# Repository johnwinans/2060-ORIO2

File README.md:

# ORIO2
Open Robot IO Controller Version 2 Rev 2.

A [PDF of the schematic can be found here](2060-ORIO2.pdf).

This project contains 
[KiCad 5](https://kicad.org/) 
design files for a 
[Rasbperry PI](https://www.raspberrypi.org/products/)
add-on module that can be used to operate a robot such as those used in 
[First Robotics Competition](https://www.firstinspires.org/robotics/frc).

The ORIO2 adds the following I/O ports to a Raspberry PI:

* 10 5V tolerant LVTTL quadrature inputs with 3.3v or 5v power
* 8 5V tolerant LVTTL digital inputs with 3.3v or 5v power
* 8 LVTTL digital outputs with 3.3v or 5v power
* 16 direct-FPGA GPIO pins on header with 3.3v power
* 1 Power LED
* 8 User LED outputs
* 8 User switch (binary inputs)
* 2 User push-button (binary inputs)
* 8 ADC inputs 0-5V (w/jumper on port 0 to monitor battery voltage)
* 16 PWM outputs w/6V, 3A power
* 1 12V RSL light output
* 8 24V solenoid outputs
* 1 12V air-compressor relay control output
* 1 Raspberry PI I2C pinout with 3.3V power supply & pullup resistors

All I/O is controlled with a Lattice ICE40HX4K-TQ144 FPGA that 
communicates with the PI using the PI's SPI port.

The FPGA and Raspberry PI source code is open-source and managed 
using a github repo here: 
[ORIO2-software](https://github.com/johnwinans/ORIO2-software)

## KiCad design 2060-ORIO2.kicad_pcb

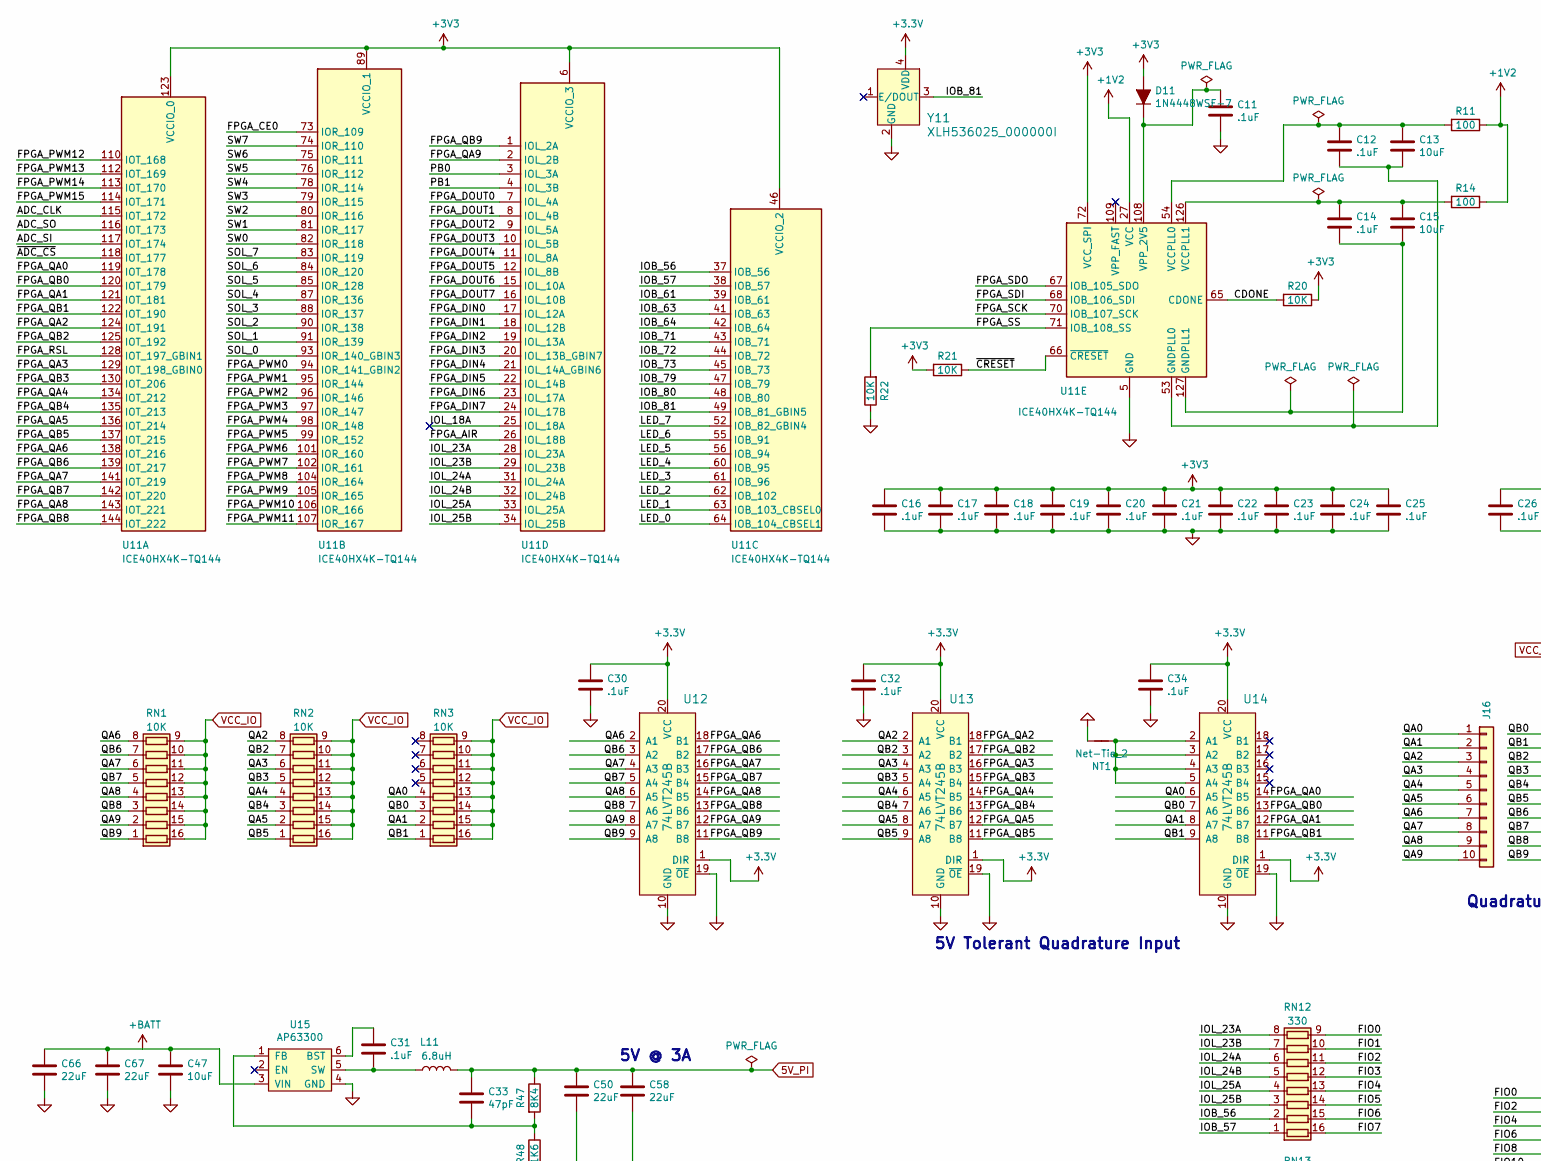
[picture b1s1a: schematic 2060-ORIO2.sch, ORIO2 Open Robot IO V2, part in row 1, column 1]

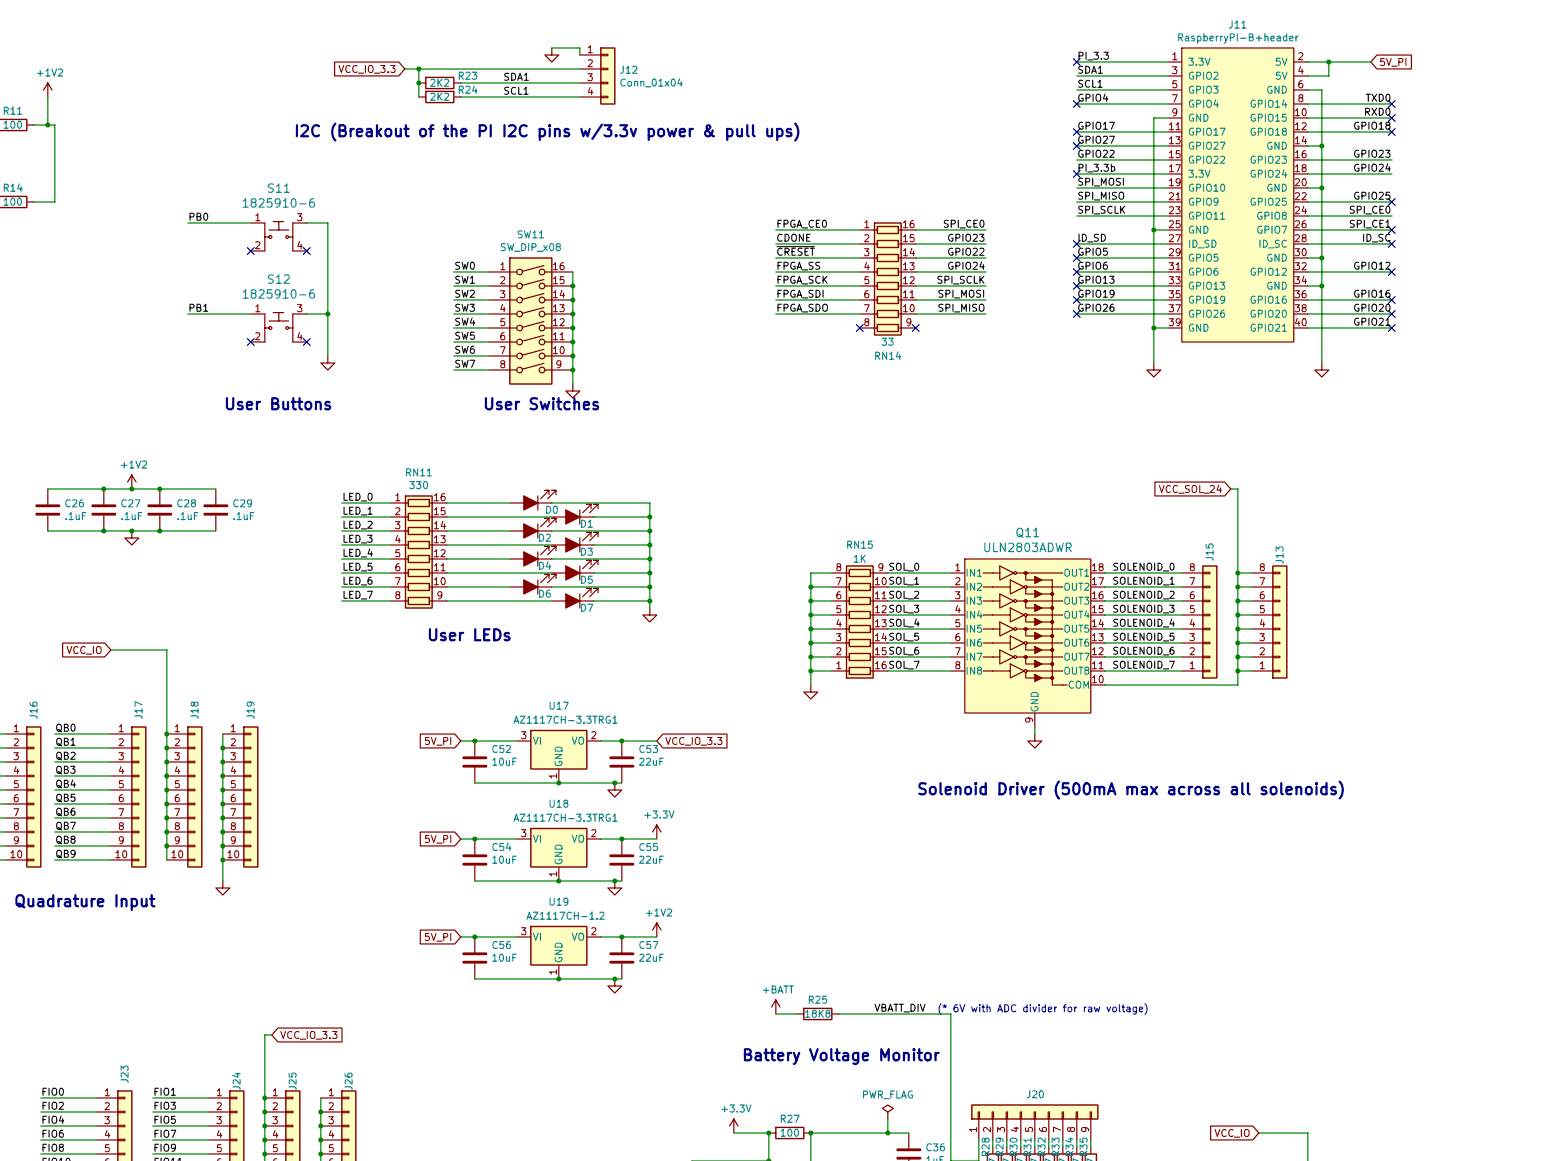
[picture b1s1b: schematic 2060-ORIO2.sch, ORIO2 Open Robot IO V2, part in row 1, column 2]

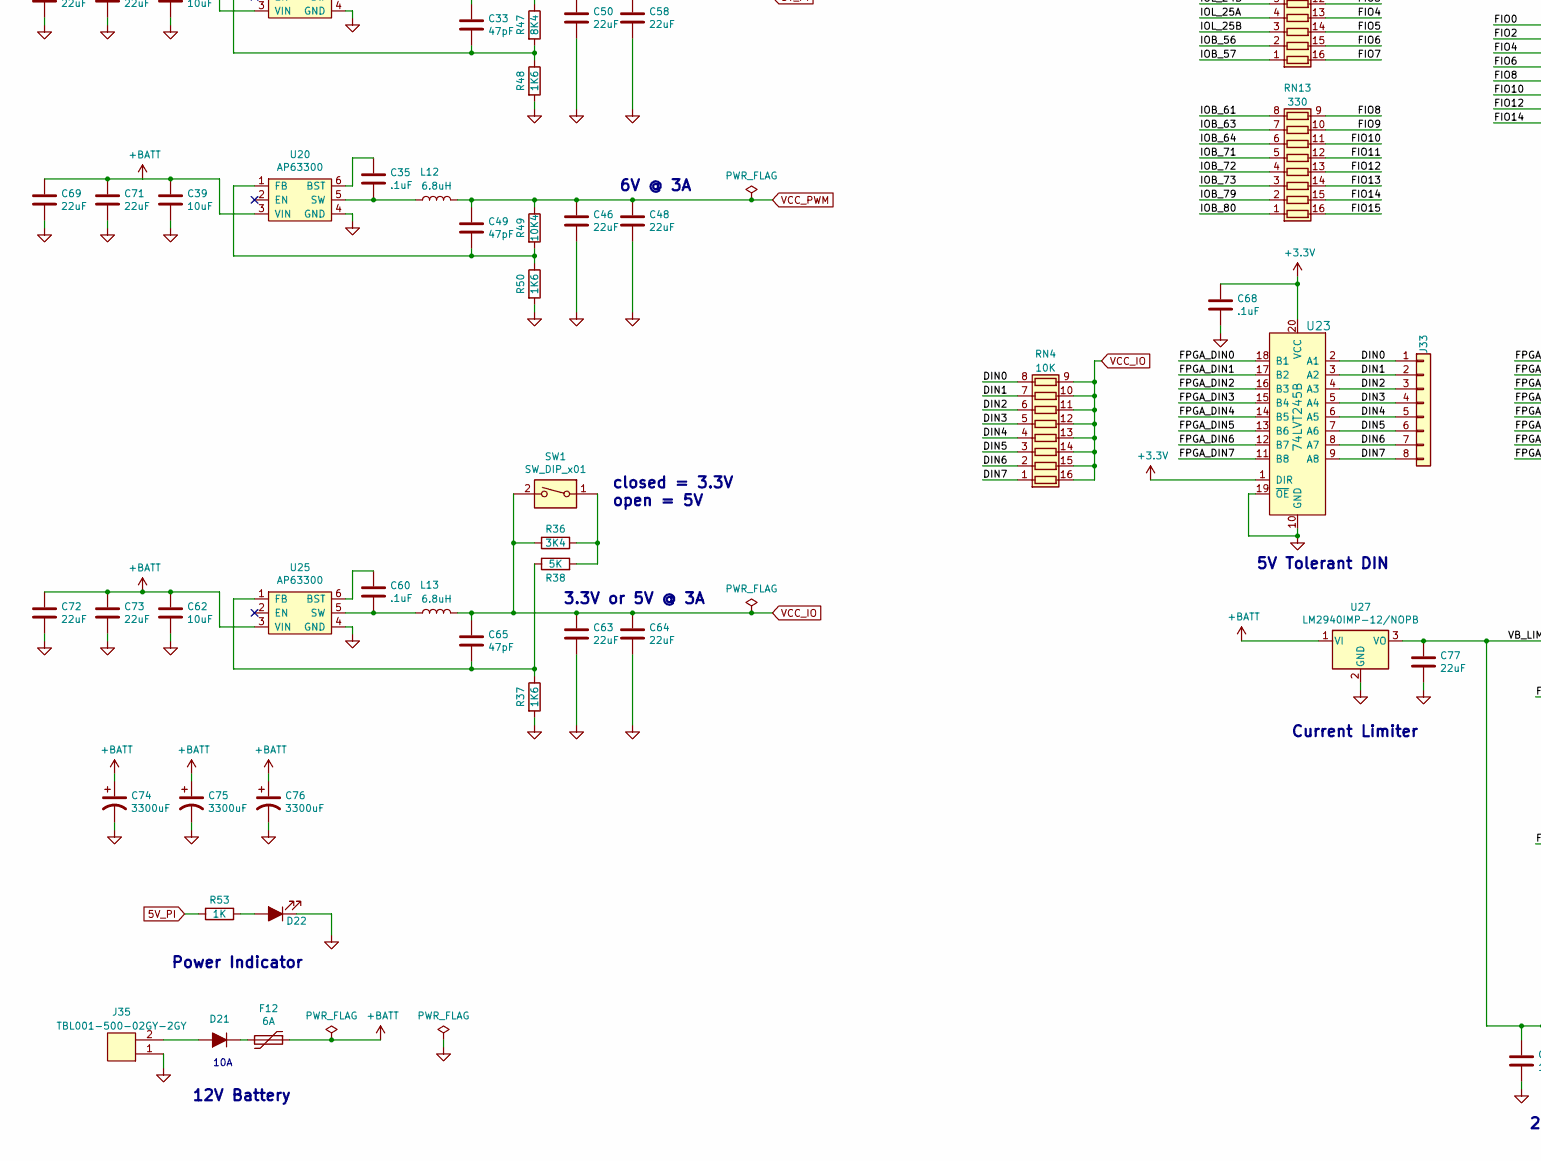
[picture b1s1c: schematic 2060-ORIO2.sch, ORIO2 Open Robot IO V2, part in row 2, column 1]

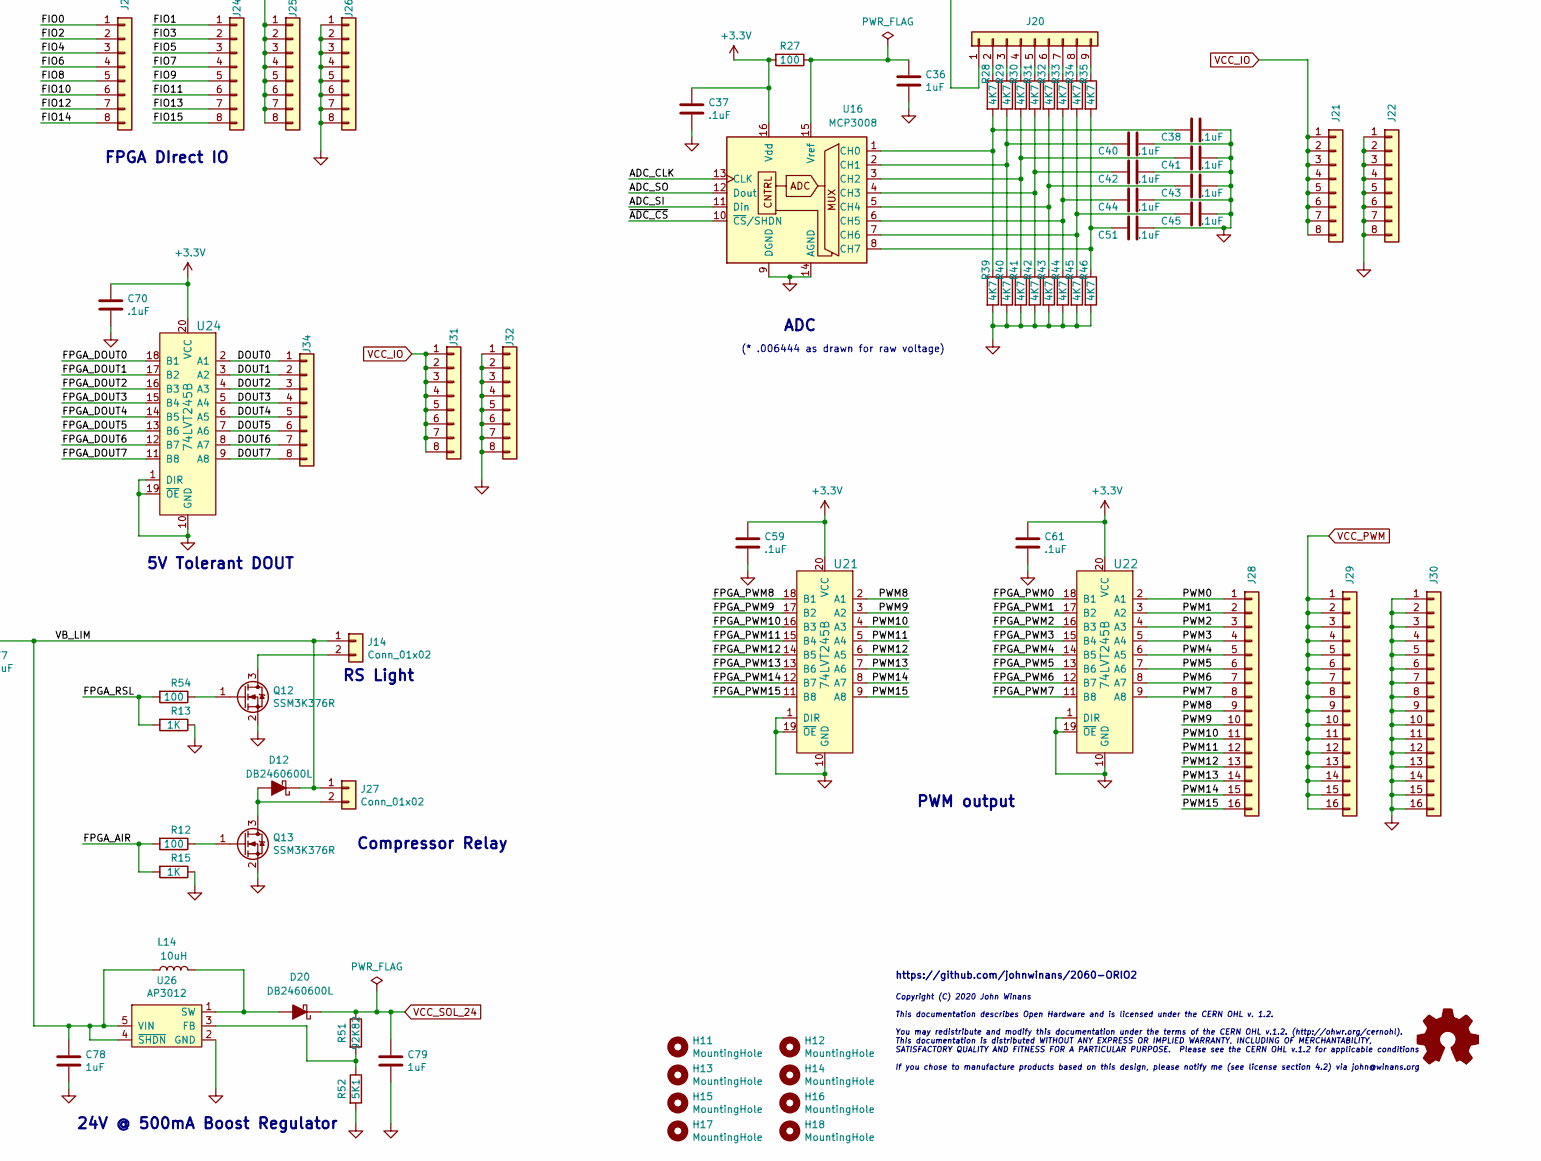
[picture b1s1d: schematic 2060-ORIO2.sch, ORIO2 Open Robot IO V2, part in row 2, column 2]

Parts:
C11, C12, C14, C16, C17, C18, C19, C20, C21, C22, C23, C24, C25, C26, C27, C28, C29, C30, C31, C32, C34, C35, C37, C38, C40, C41, C42, C43, C44, C45, C51, C59, C60, C61, C68, C70: .1uF; C_0603_1608Metric_Pad1.05x0.95mm_HandSolder; MPN C1608X5R1E104K; Digi-Key_PN 445-6854-1-ND
C13, C15, C52, C54, C56: 10uF; C_0603_1608Metric_Pad1.05x0.95mm_HandSolder; MPN CL10A106MQ8NNNC; Digi-Key_PN 1276-1119-1-ND
C33, C49, C65: 47pF; C_0603_1608Metric_Pad1.05x0.95mm_HandSolder
C36, C78, C79: 1uF; C_0603_1608Metric_Pad1.05x0.95mm_HandSolder; MPN CL10A105KA8NNNC; Digi-Key_PN 1276-1102-1-ND
C39, C47, C62: 10uF; C_0805_2012Metric_Pad1.15x1.40mm_HandSolder
C46, C48, C50, C58, C63, C64: 22uF; C_0805_2012Metric_Pad1.15x1.40mm_HandSolder; MPN GRM21BR61A226ME44L; Digi-Key_PN 490-10746-1-ND
C53, C55, C57: 22uF; C_0603_1608Metric_Pad1.05x0.95mm_HandSolder; MPN CL10A226MQ8NRNE; Digi-Key_PN 1276-2868-1-ND
C66, C67, C69, C71, C72, C73, C77: 22uF; C_0805_2012Metric_Pad1.15x1.40mm_HandSolder; Digi-Key_PN 490-14661-1-ND
C74, C75, C76: 3300uF; CP_Radial_D16.0mm_P7.50mm; MPN UVR1E332MHD; Digi-Key_PN 493-1067-ND
D0, D1, D2, D3, D4, D5, D6, D7, D22: LED_ALT; LED_0805_2012Metric_Pad1.15x1.40mm_HandSolder; MPN LG R971-KN-1; Digi-Key_PN 475-1410-1-ND
D11: 1N4448WSF-7; D_0603_1608Metric_Pad1.05x0.95mm_HandSolder; MPN 1N4448HWS-7-F; Digi-Key_PN 1N4448HWS-FDICT-ND
D12, D20: DB2460600L; D_SOD-128; MPN DB2460600L; Digi-Key_PN DB2460600LCT-ND
D21: D_ALT; D_SMC; MPN S10KC V7G; Digi-Key_PN S10KCV7GCT-ND
F12: 6A; Fuse_2920_7451Metric_Pad2.10x5.45mm_HandSolder; MPN 2920L600/12MR; Digi-Key_PN F8137CT-ND
H11, H12, H13, H14, H15, H16, H17, H18: MountingHole; MountingHole_2.7mm_M2.5; MPN x; Digi-Key_PN x
J11: RaspberryPI-B+header; PinHeader_2x20_P2.54mm_Vertical; MPN x; Digi-Key_PN x
J12: Conn_01x04; PinHeader_1x04_P2.54mm_Vertical; MPN x; Digi-Key_PN x
J13, J15, J21, J22, J23, J24, J25, J26, J31, J32, J33, J34: Conn_01x08; PinHeader_1x08_P2.54mm_Vertical; MPN x; Digi-Key_PN x
J14, J27: Conn_01x02; PinHeader_1x02_P2.54mm_Vertical; MPN x; Digi-Key_PN x
J16, J17, J18, J19: Conn_01x10; PinHeader_1x10_P2.54mm_Vertical; MPN x; Digi-Key_PN x
J20: Conn_01x09; PinHeader_1x09_P2.54mm_Vertical; MPN x; Digi-Key_PN x
J28, J29, J30: Conn_01x16; PinHeader_1x16_P2.54mm_Vertical; MPN x; Digi-Key_PN x
J35: TBL001-500-02GY-2GY; MPN TBL001-500-02GY-2GY; Digi-Key_PN 102-6360-ND
L11, L12, L13: 6.8uH; L_Bourns-SRN6028; MPN VLS6045EX-6R8M; Digi-Key_PN 445-173057-1-ND
L14: 10uH; L_Taiyo-Yuden_NR-40xx_HandSoldering; MPN NRG4026T100M; Digi-Key_PN 587-2376-1-ND
LOGO11: Logo_Open_Hardware_Small; OSHW-Logo_11.4x12mm_SilkScreen; MPN x; Digi-Key_PN x
NT1: Net-Tie_2; NetTie-2_SMD_Pad0.5mm; MPN x; Digi-Key_PN x
Q11: ULN2803ADWR; SOIC-18_W7.5mm; MPN ULN2803ADWR; Digi-Key_PN 296-15777-1-ND
Q12, Q13: SSM3K376R; SOT-23; MPN ‎SSM3K376R,LF; Digi-Key_PN SSM3K376RLFCT-ND‎
R11, R14, R27: 100; R_0603_1608Metric_Pad1.05x0.95mm_HandSolder; MPN RC0603FR-07100RL; Digi-Key_PN 311-100HRCT-ND
R12, R54: 100; R_0603_1608Metric_Pad0.98x0.95mm_HandSolder; MPN RC0603FR-07100RL; Digi-Key_PN 311-100HRCT-ND
R13, R15: 1K; R_0603_1608Metric_Pad0.98x0.95mm_HandSolder
R20, R21, R22: 10K; R_0603_1608Metric_Pad1.05x0.95mm_HandSolder; MPN RC0603FR-0710KL; Digi-Key_PN 311-10.0KHRCT-ND
R23, R24: 2K2; R_0603_1608Metric_Pad1.05x0.95mm_HandSolder; MPN RC0603FR-072K2L; Digi-Key_PN 311-2.20KHRCT-ND
R25: 18K8; R_0603_1608Metric_Pad1.05x0.95mm_HandSolder; MPN RC0603FR-0718KL; Digi-Key_PN 311-18.0KHRCT-ND
R28, R29, R30, R31, R32, R33, R34, R35, R39, R40, R41, R42, R43, R44, R45, R46: 4K7; R_0603_1608Metric_Pad1.05x0.95mm_HandSolder; MPN RC0603FR-074K7L; Digi-Key_PN 311-4.70KHRCT-ND
R36: 3K4; R_0603_1608Metric_Pad1.05x0.95mm_HandSolder; MPN RMCF0603FT3K40; Digi-Key_PN RMCF0603FT3K40CT-ND
R37, R48, R50: 1K6; R_0603_1608Metric_Pad1.05x0.95mm_HandSolder; MPN RMCF0603FT1K60; Digi-Key_PN RMCF0603FT1K60CT-ND
R38: 5K; R_0603_1608Metric_Pad1.05x0.95mm_HandSolder; MPN CR0603-FX-5101ELF; Digi-Key_PN CR0603-FX-5101ELFCT-ND
R47: 8K4; R_0603_1608Metric_Pad1.05x0.95mm_HandSolder; MPN RMCF0603FT8K45; Digi-Key_PN RMCF0603FT8K45CT-ND
R49: 10K4; R_0603_1608Metric_Pad1.05x0.95mm_HandSolder; MPN RMCF0603FT10K5; Digi-Key_PN RMCF0603FT10K5CT-ND
R51: 92K82; R_0603_1608Metric_Pad1.05x0.95mm_HandSolder; MPN RMCF0603FT90K9; Digi-Key_PN RMCF0603FT90K9CT-ND
R52: 5K1; R_0603_1608Metric_Pad1.05x0.95mm_HandSolder; MPN CR0603-FX-5101ELF; Digi-Key_PN CR0603-FX-5101ELFCT-ND
R53: 1K; R_0603_1608Metric_Pad1.05x0.95mm_HandSolder; MPN RC0603FR-071KL; Digi-Key_PN 311-1.00KHRCT-ND
RN1, RN2, RN3, RN4: 10K; R_Array_Convex_8x0602; MPN EXB-2HV103JV; Digi-Key_PN Y1103CT-ND
RN11, RN12, RN13: 330; R_Array_Convex_8x0602; MPN EXB-2HV331JV; Digi-Key_PN Y1331CT-ND
RN14: 33; R_Array_Convex_8x0602; MPN EXB-2HV330JV; Digi-Key_PN Y1330CT-ND
RN15: 1K; R_Array_Convex_8x0602; MPN EXB-2HV102JV; Digi-Key_PN Y1102CT-ND
S11, S12: 1825910-6; Switch_Tactile_THT_6x6mm; MPN 1825910-6; Digi-Key_PN 450-1650-ND
SW1: SW_DIP_x01; SW_DIP_SPSTx01_Slide_6.7x4.1mm_W7.62mm_P2.54mm_LowProfile; MPN DS04-254-1L-01BK; Digi-Key_PN 2223-DS04-254-1L-01BK-ND
SW11: SW_DIP_x08; SW_DIP_SPSTx08_Slide_6.7x21.88mm_W7.62mm_P2.54mm_LowProfile; MPN 210-8MS; Digi-Key_PN CT2108MS-ND
U11: ICE40HX4K-TQ144; TQFP-144_20x20mm_P0.5mm; MPN ICE40HX4K-TQ144; Digi-Key_PN 220-1572-ND
U12, U13, U14, U21, U22, U23, U24: ‎74LVT245B; TSSOP-20_4.4x6.5mm_P0.65mm; MPN 74LVT245BPW,118; Digi-Key_PN 1727-6005-1-ND
U15, U20, U25: AP63300; SOT-23-6; MPN AP63300WU-7; Digi-Key_PN 31-AP63300WU-7CT-ND
U16: MCP3008; SOIC-16_3.9x9.9mm_P1.27mm; MPN MCP3008-I/SL; Digi-Key_PN MCP3008-I/SL-ND
U17, U18: AZ1117CH-3.3TRG1; SOT-223-3_TabPin2; MPN AZ1117CH-3.3TRG1; Digi-Key_PN AZ1117CH-3.3TRG1DICT-ND
U19: AZ1117CH-1.2; SOT-223-3_TabPin2; MPN AZ1117CH-1.2TRG1; Digi-Key_PN AZ1117CH-1.2TRG1DICT-ND
U26: AP3012; SOT-23-5; MPN AP3012KTR-G1; Digi-Key_PN AP3012KTR-G1DICT-ND
U27: LM2940IMP-12/NOPB; TO-252-3_TabPin2; MPN LM2940IMP-12/NOPB; Digi-Key_PN LM2940IMP-12/NOPBCT-ND
Y11: XLH536025_000000I; Oscillator_XLH536025.000000I; MPN XLH536025.000000I; Digi-Key_PN 631-1156-1-ND

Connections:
5V_PI: C33.1, C50.1, C52.1, C54.1, C56.1, C58.1, J11.2 (5V), J11.4 (5V), L11.2, R47.1, R53.2, U17.3 (VI), U18.3 (VI), U19.3 (VI)
+1V2: C26.1, C27.1, C28.1, C29.1, C57.1, R11.1, R14.1, U11.27 (VCC), U11.40 (VCC), U11.92 (VCC), U11.111 (VCC), U19.2 (VO)
+BATT: C39.1, C47.1, C62.1, C66.1, C67.1, C69.1, C71.1, C72.1, C73.1, C74.1, C75.1, C76.1, F12.1, R25.2, U15.3 (VIN), U20.3 (VIN), U25.3 (VIN), U27.1 (VI)
/ADC_CLK: U11.115 (IOT_172), U16.13 (CLK)
/ADC_SI: U11.117 (IOT_174), U16.11 (Din)
/ADC_SO: U11.116 (IOT_173), U16.12 (Dout)
/CDONE: R20.2, RN14.2 (R2.1), U11.65 (CDONE)
/DIN0: J33.1, RN4.8 (R8.1), U23.2 (A1)
/DIN1: J33.2, RN4.7 (R7.1), U23.3 (A2)
/DIN2: J33.3, RN4.6 (R6.1), U23.4 (A3)
/DIN3: J33.4, RN4.5 (R5.1), U23.5 (A4)
/DIN4: J33.5, RN4.4 (R4.1), U23.6 (A5)
/DIN5: J33.6, RN4.3 (R3.1), U23.7 (A6)
/DIN6: J33.7, RN4.2 (R2.1), U23.8 (A7)
/DIN7: J33.8, RN4.1 (R1.1), U23.9 (A8)
/DOUT0: J34.1, U24.2 (A1)
/DOUT1: J34.2, U24.3 (A2)
/DOUT2: J34.3, U24.4 (A3)
/DOUT3: J34.4, U24.5 (A4)
/DOUT4: J34.5, U24.6 (A5)
/DOUT5: J34.6, U24.7 (A6)
/DOUT6: J34.7, U24.8 (A7)
/DOUT7: J34.8, U24.9 (A8)
/FIO0: J23.1, RN12.9 (R8.2)
/FIO1: J24.1, RN12.10 (R7.2)
/FIO2: J23.2, RN12.11 (R6.2)
/FIO3: J24.2, RN12.12 (R5.2)
/FIO4: J23.3, RN12.13 (R4.2)
/FIO5: J24.3, RN12.14 (R3.2)
/FIO6: J23.4, RN12.15 (R2.2)
/FIO7: J24.4, RN12.16 (R1.2)
/FIO8: J23.5, RN13.9 (R8.2)
/FIO9: J24.5, RN13.10 (R7.2)
/FIO10: J23.6, RN13.11 (R6.2)
/FIO11: J24.6, RN13.12 (R5.2)
/FIO12: J23.7, RN13.13 (R4.2)
/FIO13: J24.7, RN13.14 (R3.2)
/FIO14: J23.8, RN13.15 (R2.2)
/FIO15: J24.8, RN13.16 (R1.2)
/FPGA_AIR: R12.2, R15.2, U11.26 (IOL_18B)
/FPGA_CE0: RN14.1 (R1.1), U11.73 (IOR_109)
/FPGA_DIN0: U11.17 (IOL_12A), U23.18 (B1)
/FPGA_DIN1: U11.18 (IOL_12B), U23.17 (B2)
/FPGA_DIN2: U11.19 (IOL_13A), U23.16 (B3)
/FPGA_DIN3: U11.20 (IOL_13B_GBIN7), U23.15 (B4)
/FPGA_DIN4: U11.21 (IOL_14A_GBIN6), U23.14 (B5)
/FPGA_DIN5: U11.22 (IOL_14B), U23.13 (B6)
/FPGA_DIN6: U11.23 (IOL_17A), U23.12 (B7)
/FPGA_DIN7: U11.24 (IOL_17B), U23.11 (B8)
/FPGA_DOUT0: U11.7 (IOL_4A), U24.18 (B1)
/FPGA_DOUT1: U11.8 (IOL_4B), U24.17 (B2)
/FPGA_DOUT2: U11.9 (IOL_5A), U24.16 (B3)
/FPGA_DOUT3: U11.10 (IOL_5B), U24.15 (B4)
/FPGA_DOUT4: U11.11 (IOL_8A), U24.14 (B5)
/FPGA_DOUT5: U11.12 (IOL_8B), U24.13 (B6)
/FPGA_DOUT6: U11.15 (IOL_10A), U24.12 (B7)
/FPGA_DOUT7: U11.16 (IOL_10B), U24.11 (B8)
/FPGA_PWM0: U11.94 (IOR_141_GBIN2), U22.18 (B1)
/FPGA_PWM1: U11.95 (IOR_144), U22.17 (B2)
/FPGA_PWM2: U11.96 (IOR_146), U22.16 (B3)
/FPGA_PWM3: U11.97 (IOR_147), U22.15 (B4)
/FPGA_PWM4: U11.98 (IOR_148), U22.14 (B5)
/FPGA_PWM5: U11.99 (IOR_152), U22.13 (B6)
/FPGA_PWM6: U11.101 (IOR_160), U22.12 (B7)
/FPGA_PWM7: U11.102 (IOR_161), U22.11 (B8)
/FPGA_PWM8: U11.104 (IOR_164), U21.18 (B1)
/FPGA_PWM9: U11.105 (IOR_165), U21.17 (B2)
/FPGA_PWM10: U11.106 (IOR_166), U21.16 (B3)
/FPGA_PWM11: U11.107 (IOR_167), U21.15 (B4)
/FPGA_PWM12: U11.110 (IOT_168), U21.14 (B5)
/FPGA_PWM13: U11.112 (IOT_169), U21.13 (B6)
/FPGA_PWM14: U11.113 (IOT_170), U21.12 (B7)
/FPGA_PWM15: U11.114 (IOT_171), U21.11 (B8)
/FPGA_QA0: U11.119 (IOT_178), U14.14 (B5)
/FPGA_QA1: U11.121 (IOT_181), U14.12 (B7)
/FPGA_QA2: U11.124 (IOT_191), U13.18 (B1)
/FPGA_QA3: U11.129 (IOT_198_GBIN0), U13.16 (B3)
/FPGA_QA4: U11.134 (IOT_212), U13.14 (B5)
/FPGA_QA5: U11.136 (IOT_214), U13.12 (B7)
/FPGA_QA6: U11.138 (IOT_216), U12.18 (B1)
/FPGA_QA7: U11.141 (IOT_219), U12.16 (B3)
/FPGA_QA8: U11.143 (IOT_221), U12.14 (B5)
/FPGA_QA9: U11.2 (IOL_2B), U12.12 (B7)
/FPGA_QB0: U11.120 (IOT_179), U14.13 (B6)
/FPGA_QB1: U11.122 (IOT_190), U14.11 (B8)
/FPGA_QB2: U11.125 (IOT_192), U13.17 (B2)
/FPGA_QB3: U11.130 (IOT_206), U13.15 (B4)
/FPGA_QB4: U11.135 (IOT_213), U13.13 (B6)
/FPGA_QB5: U11.137 (IOT_215), U13.11 (B8)
/FPGA_QB6: U11.139 (IOT_217), U12.17 (B2)
/FPGA_QB7: U11.142 (IOT_220), U12.15 (B4)
/FPGA_QB8: U11.144 (IOT_222), U12.13 (B6)
/FPGA_QB9: U11.1 (IOL_2A), U12.11 (B8)
/FPGA_RSL: R13.2, R54.2, U11.128 (IOT_197_GBIN1)
/FPGA_SCK: RN14.5 (R5.1), U11.70 (IOB_107_SCK)
/FPGA_SDI: RN14.6 (R6.1), U11.68 (IOB_106_SDI)
/FPGA_SDO: RN14.7 (R7.1), U11.67 (IOB_105_SDO)
/FPGA_SS: R22.2, RN14.4 (R4.1), U11.71 (IOB_108_SS)
/GPIO4: J11.7 (GPIO4)
/GPIO5: J11.29 (GPIO5)
/GPIO6: J11.31 (GPIO6)
/GPIO12: J11.32 (GPIO12)
/GPIO13: J11.33 (GPIO13)
/GPIO16: J11.36 (GPIO16)
/GPIO17: J11.11 (GPIO17)
/GPIO18: J11.12 (GPIO18)
/GPIO19: J11.35 (GPIO19)
/GPIO20: J11.38 (GPIO20)
/GPIO21: J11.40 (GPIO21)
/GPIO22: J11.15 (GPIO22), RN14.14 (R3.2)
/GPIO23: J11.16 (GPIO23), RN14.15 (R2.2)
/GPIO24: J11.18 (GPIO24), RN14.13 (R4.2)
/GPIO25: J11.22 (GPIO25)
/GPIO26: J11.37 (GPIO26)
/GPIO27: J11.13 (GPIO27)
/ID_SC: J11.28 (ID_SC)
/ID_SD: J11.27 (ID_SD)
/IOB_56: RN12.2 (R2.1), U11.37 (IOB_56)
/IOB_57: RN12.1 (R1.1), U11.38 (IOB_57)
/IOB_61: RN13.8 (R8.1), U11.39 (IOB_61)
/IOB_63: RN13.7 (R7.1), U11.41 (IOB_63)
/IOB_64: RN13.6 (R6.1), U11.42 (IOB_64)
/IOB_71: RN13.5 (R5.1), U11.43 (IOB_71)
/IOB_72: RN13.4 (R4.1), U11.44 (IOB_72)
/IOB_73: RN13.3 (R3.1), U11.45 (IOB_73)
/IOB_79: RN13.2 (R2.1), U11.47 (IOB_79)
/IOB_80: RN13.1 (R1.1), U11.48 (IOB_80)
/IOB_81: U11.49 (IOB_81_GBIN5), Y11.3 (OUT)
/IOL_18A: U11.25 (IOL_18A)
/IOL_23A: RN12.8 (R8.1), U11.28 (IOL_23A)
/IOL_23B: RN12.7 (R7.1), U11.29 (IOL_23B)
/IOL_24A: RN12.6 (R6.1), U11.31 (IOL_24A)
/IOL_24B: RN12.5 (R5.1), U11.32 (IOL_24B)
/IOL_25A: RN12.4 (R4.1), U11.33 (IOL_25A)
/IOL_25B: RN12.3 (R3.1), U11.34 (IOL_25B)
/LED_0: RN11.1 (R1.1), U11.64 (IOB_104_CBSEL1)
/LED_1: RN11.2 (R2.1), U11.63 (IOB_103_CBSEL0)
/LED_2: RN11.3 (R3.1), U11.62 (IOB_102)
/LED_3: RN11.4 (R4.1), U11.61 (IOB_96)
/LED_4: RN11.5 (R5.1), U11.60 (IOB_95)
/LED_5: RN11.6 (R6.1), U11.56 (IOB_94)
/LED_6: RN11.7 (R7.1), U11.55 (IOB_91)
/LED_7: RN11.8 (R8.1), U11.52 (IOB_82_GBIN4)
/PB0: S11.1, U11.3 (IOL_3A)
/PB1: S12.1, U11.4 (IOL_3B)
/PI_3.3: J11.1 (3.3V)
/PI_3.3b: J11.17 (3.3V)
/PWM0: J28.1, U22.2 (A1)
/PWM1: J28.2, U22.3 (A2)
/PWM2: J28.3, U22.4 (A3)
/PWM3: J28.4, U22.5 (A4)
/PWM4: J28.5, U22.6 (A5)
/PWM5: J28.6, U22.7 (A6)
/PWM6: J28.7, U22.8 (A7)
/PWM7: J28.8, U22.9 (A8)
/PWM8: J28.9, U21.2 (A1)
/PWM9: J28.10, U21.3 (A2)
/PWM10: J28.11, U21.4 (A3)
/PWM11: J28.12, U21.5 (A4)
/PWM12: J28.13, U21.6 (A5)
/PWM13: J28.14, U21.7 (A6)
/PWM14: J28.15, U21.8 (A7)
/PWM15: J28.16, U21.9 (A8)
/QA0: J16.1, RN3.4 (R4.1), U14.6 (A5)
/QA1: J16.2, RN3.2 (R2.1), U14.8 (A7)
/QA2: J16.3, RN2.8 (R8.1), U13.2 (A1)
/QA3: J16.4, RN2.6 (R6.1), U13.4 (A3)
/QA4: J16.5, RN2.4 (R4.1), U13.6 (A5)
/QA5: J16.6, RN2.2 (R2.1), U13.8 (A7)
/QA6: J16.7, RN1.8 (R8.1), U12.2 (A1)
/QA7: J16.8, RN1.6 (R6.1), U12.4 (A3)
/QA8: J16.9, RN1.4 (R4.1), U12.6 (A5)
/QA9: J16.10, RN1.2 (R2.1), U12.8 (A7)
/QB0: J17.1, RN3.3 (R3.1), U14.7 (A6)
/QB1: J17.2, RN3.1 (R1.1), U14.9 (A8)
/QB2: J17.3, RN2.7 (R7.1), U13.3 (A2)
/QB3: J17.4, RN2.5 (R5.1), U13.5 (A4)
/QB4: J17.5, RN2.3 (R3.1), U13.7 (A6)
/QB5: J17.6, RN2.1 (R1.1), U13.9 (A8)
/QB6: J17.7, RN1.7 (R7.1), U12.3 (A2)
/QB7: J17.8, RN1.5 (R5.1), U12.5 (A4)
/QB8: J17.9, RN1.3 (R3.1), U12.7 (A6)
/QB9: J17.10, RN1.1 (R1.1), U12.9 (A8)
/RXD0: J11.10 (GPIO15)
/SCL1: J11.5 (GPIO3), J12.4, R24.1
/SDA1: J11.3 (GPIO2), J12.3, R23.1
/SOLENOID_0: J15.8, Q11.18 (OUT1)
/SOLENOID_1: J15.7, Q11.17 (OUT2)
/SOLENOID_2: J15.6, Q11.16 (OUT3)
/SOLENOID_3: J15.5, Q11.15 (OUT4)
/SOLENOID_4: J15.4, Q11.14 (OUT5)
/SOLENOID_5: J15.3, Q11.13 (OUT6)
/SOLENOID_6: J15.2, Q11.12 (OUT7)
/SOLENOID_7: J15.1, Q11.11 (OUT8)
/SOL_0: Q11.1 (IN1), RN15.9 (R8.2), U11.93 (IOR_140_GBIN3)
/SOL_1: Q11.2 (IN2), RN15.10 (R7.2), U11.91 (IOR_139)
/SOL_2: Q11.3 (IN3), RN15.11 (R6.2), U11.90 (IOR_138)
/SOL_3: Q11.4 (IN4), RN15.12 (R5.2), U11.88 (IOR_137)
/SOL_4: Q11.5 (IN5), RN15.13 (R4.2), U11.87 (IOR_136)
/SOL_5: Q11.6 (IN6), RN15.14 (R3.2), U11.85 (IOR_128)
/SOL_6: Q11.7 (IN7), RN15.15 (R2.2), U11.84 (IOR_120)
/SOL_7: Q11.8 (IN8), RN15.16 (R1.2), U11.83 (IOR_119)
/SPI_CE0: J11.24 (GPIO8), RN14.16 (R1.2)
/SPI_CE1: J11.26 (GPIO7)
/SPI_MISO: J11.21 (GPIO9), RN14.10 (R7.2)
/SPI_MOSI: J11.19 (GPIO10), RN14.11 (R6.2)
/SPI_SCLK: J11.23 (GPIO11), RN14.12 (R5.2)
/SW0: SW11.1, U11.82 (IOR_118)
/SW1: SW11.2, U11.81 (IOR_117)
/SW2: SW11.3, U11.80 (IOR_116)
/SW3: SW11.4, U11.79 (IOR_115)
/SW4: SW11.5, U11.78 (IOR_114)
/SW5: SW11.6, U11.76 (IOR_112)
/SW6: SW11.7, U11.75 (IOR_111)
/SW7: SW11.8, U11.74 (IOR_110)
/TXD0: J11.8 (GPIO14)
/VBATT_DIV: J20.1, R25.1
/VB_LIM: C77.1, C78.1, D12.1 (K), J14.1, J27.1, L14.1, U26.4 (~SHDN), U26.5 (VIN), U27.3 (VO)
/~ADC_CS: U11.118 (IOT_177), U16.10 (~CS~/SHDN)
/~CRESET~: R21.1, RN14.3 (R3.1), U11.66 (~CRESET)
GND: C11.2, C16.2, C17.2, C18.2, C19.2, C20.2, C21.2, C22.2, C23.2, C24.2, C25.2, C26.2, C27.2, C28.2, C29.2, C30.2, C32.2, C34.2, C36.2, C37.2, C38.2, C39.2, C40.2, C41.2, C42.2, C43.2, C44.2, C45.2, C46.2, C47.2, C48.2, C50.2, C51.2, C52.2, C53.2, C54.2, C55.2, C56.2, C57.2, C58.2, C59.2, C61.2, C62.2, C63.2, C64.2, C66.2, C67.2, C68.2, C69.2, C70.2, C71.2, C72.2, C73.2, C74.2, C75.2, C76.2, C77.2, C78.2, C79.2, D0.1 (K), D1.1 (K), D2.1 (K), D3.1 (K), D4.1 (K), D5.1 (K), D6.1 (K), D7.1 (K), D22.1 (K), J11.6 (GND), J11.9 (GND), J11.14 (GND), J11.20 (GND), J11.25 (GND), J11.30 (GND), J11.34 (GND), J11.39 (GND), J12.1, J19.1, J19.2, J19.3, J19.4, J19.5, J19.6, J19.7, J19.8, J19.9, J19.10, J22.1, J22.2, J22.3, J22.4, J22.5, J22.6, J22.7, J22.8, J26.1, J26.2, J26.3, J26.4, J26.5, J26.6, J26.7, J26.8, J30.1, J30.2, J30.3, J30.4, J30.5, J30.6, J30.7, J30.8, J30.9, J30.10, J30.11, J30.12, J30.13, J30.14, J30.15, J30.16, J32.1, J32.2, J32.3, J32.4, J32.5, J32.6, J32.7, J32.8, J35.1, NT1.1, Q11.9 (GND), Q12.2 (S), Q13.2 (S), R13.1, R15.1, R22.1, R37.2, R39.2, R40.2, R41.2, R42.2, R43.2, R44.2, R45.2, R46.2, R48.2, R50.2, R52.2, RN15.1 (R1.1), RN15.2 (R2.1), RN15.3 (R3.1), RN15.4 (R4.1), RN15.5 (R5.1), RN15.6 (R6.1), RN15.7 (R7.1), RN15.8 (R8.1), S11.3, S12.3, SW11.9, SW11.10, SW11.11, SW11.12, SW11.13, SW11.14, SW11.15, SW11.16, U11.5 (GND), U11.13 (GND), U11.14 (GND), U11.59 (GND), U11.69 (GND), U11.86 (GND), U11.103 (GND), U11.132 (GND), U11.140 (GND), U12.10 (GND), U12.19 (~OE), U13.10 (GND), U13.19 (~OE), U14.10 (GND), U14.19 (~OE), U15.4 (GND), U16.9 (DGND), U16.14 (AGND), U17.1 (GND), U18.1 (GND), U19.1 (GND), U20.4 (GND), U21.1 (DIR), U21.10 (GND), U21.19 (~OE), U22.1 (DIR), U22.10 (GND), U22.19 (~OE), U23.10 (GND), U23.19 (~OE), U24.1 (DIR), U24.10 (GND), U24.19 (~OE), U25.4 (GND), U26.2 (GND), U27.2 (GND), Y11.2 (GND)
unnamed: C11.1, D11.1 (K), U11.108 (VPP_2V5)
unnamed: C12.1, C13.1, R11.2, U11.54 (VCCPLL0)
unnamed: C12.2, C13.2, U11.53 (GNDPLL0)
unnamed: C14.1, C15.1, R14.2, U11.126 (VCCPLL1)
unnamed: C14.2, C15.2, U11.127 (GNDPLL1)
unnamed: C31.1, U15.6 (BST)
unnamed: C31.2, L11.1, U15.5 (SW)
unnamed: C33.2, R47.2, R48.1, U15.1 (FB)
unnamed: C35.1, U20.6 (BST)
unnamed: C35.2, L12.1, U20.5 (SW)
unnamed: C36.1, R27.1, U16.15 (Vref)
unnamed: C38.1, R28.2, R39.1, U16.1 (CH0)
unnamed: C40.1, R29.2, R40.1, U16.2 (CH1)
unnamed: C41.1, R30.2, R41.1, U16.3 (CH2)
unnamed: C42.1, R31.2, R42.1, U16.4 (CH3)
unnamed: C43.1, R32.2, R43.1, U16.5 (CH4)
unnamed: C44.1, R33.2, R44.1, U16.6 (CH5)
unnamed: C45.1, R34.2, R45.1, U16.7 (CH6)
unnamed: C49.2, R49.2, R50.1, U20.1 (FB)
unnamed: C51.1, R35.2, R46.1, U16.8 (CH7)
unnamed: C60.1, U25.6 (BST)
unnamed: C60.2, L13.1, U25.5 (SW)
unnamed: C65.2, R37.1, R38.1, U25.1 (FB)
unnamed: D0.2 (A), RN11.16 (R1.2)
unnamed: D1.2 (A), RN11.15 (R2.2)
unnamed: D2.2 (A), RN11.14 (R3.2)
unnamed: D3.2 (A), RN11.13 (R4.2)
unnamed: D4.2 (A), RN11.12 (R5.2)
unnamed: D5.2 (A), RN11.11 (R6.2)
unnamed: D6.2 (A), RN11.10 (R7.2)
unnamed: D7.2 (A), RN11.9 (R8.2)
unnamed: D12.2 (A), J27.2, Q13.3 (D)
unnamed: D20.2 (A), L14.2, U26.1 (SW)
unnamed: D21.1 (K), F12.2
unnamed: D21.2 (A), J35.2
unnamed: D22.2 (A), R53.1
unnamed: J14.2, Q12.3 (D)
unnamed: J20.2, R28.1
unnamed: J20.3, R29.1
unnamed: J20.4, R30.1
unnamed: J20.5, R31.1
unnamed: J20.6, R32.1
unnamed: J20.7, R33.1
unnamed: J20.8, R34.1
unnamed: J20.9, R35.1
unnamed: NT1.2, U14.2 (A1), U14.3 (A2), U14.4 (A3), U14.5 (A4)
unnamed: Q12.1 (G), R54.1
unnamed: Q13.1 (G), R12.1
unnamed: R36.1, R38.2, SW1.1
unnamed: R51.2, R52.1, U26.3 (FB)
VCC_IO: C63.1, C64.1, C65.1, J18.1, J18.2, J18.3, J18.4, J18.5, J18.6, J18.7, J18.8, J18.9, J18.10, J21.1, J21.2, J21.3, J21.4, J21.5, J21.6, J21.7, J21.8, J31.1, J31.2, J31.3, J31.4, J31.5, J31.6, J31.7, J31.8, L13.2, R36.2, RN1.9 (R8.2), RN1.10 (R7.2), RN1.11 (R6.2), RN1.12 (R5.2), RN1.13 (R4.2), RN1.14 (R3.2), RN1.15 (R2.2), RN1.16 (R1.2), RN2.9 (R8.2), RN2.10 (R7.2), RN2.11 (R6.2), RN2.12 (R5.2), RN2.13 (R4.2), RN2.14 (R3.2), RN2.15 (R2.2), RN2.16 (R1.2), RN3.9 (R8.2), RN3.10 (R7.2), RN3.11 (R6.2), RN3.12 (R5.2), RN3.13 (R4.2), RN3.14 (R3.2), RN3.15 (R2.2), RN3.16 (R1.2), RN4.9 (R8.2), RN4.10 (R7.2), RN4.11 (R6.2), RN4.12 (R5.2), RN4.13 (R4.2), RN4.14 (R3.2), RN4.15 (R2.2), RN4.16 (R1.2), SW1.2
VCC_IO_3.3: C53.1, J12.2, J25.1, J25.2, J25.3, J25.4, J25.5, J25.6, J25.7, J25.8, R23.2, R24.2, U17.2 (VO)
VCC_PWM: C46.1, C48.1, C49.1, J29.1, J29.2, J29.3, J29.4, J29.5, J29.6, J29.7, J29.8, J29.9, J29.10, J29.11, J29.12, J29.13, J29.14, J29.15, J29.16, L12.2, R49.1
VCC_SOL_24: C79.1, D20.1 (K), J13.1, J13.2, J13.3, J13.4, J13.5, J13.6, J13.7, J13.8, Q11.10 (COM), R51.1

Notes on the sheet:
Copyright (C) 2020 John Winans This documentation describes Open Hardware and is licensed under the CERN OHL v. 1.2. You may redistribute and modify this documentation under the terms of the CERN OHL v.1.2. (http://ohwr.org/cernohl). This documentation is distributed WITHOUT ANY EXPRESS OR IMPLIED 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
https://github.com/johnwinans/2060-ORIO2
I2C (Breakout of the PI I2C pins w/3.3v power & pull ups)
Battery Voltage Monitor
Quadrature Input
ADC
Solenoid Driver (500mA max across all solenoids)
5V Tolerant DOUT
5V Tolerant DIN
12V Battery
10A
User Buttons
User LEDs
User Switches
6V @ 3A
5V Tolerant Quadrature Input
PWM output
closed = 3.3V open = 5V
FPGA DIrect IO
24V @ 500mA Boost Regulator
Power Indicator
RS Light
(* 6V with ADC divider for raw voltage)
(* .006444 as drawn for raw voltage)
5V @ 3A
Current Limiter
3.3V or 5V @ 3A
Compressor Relay

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
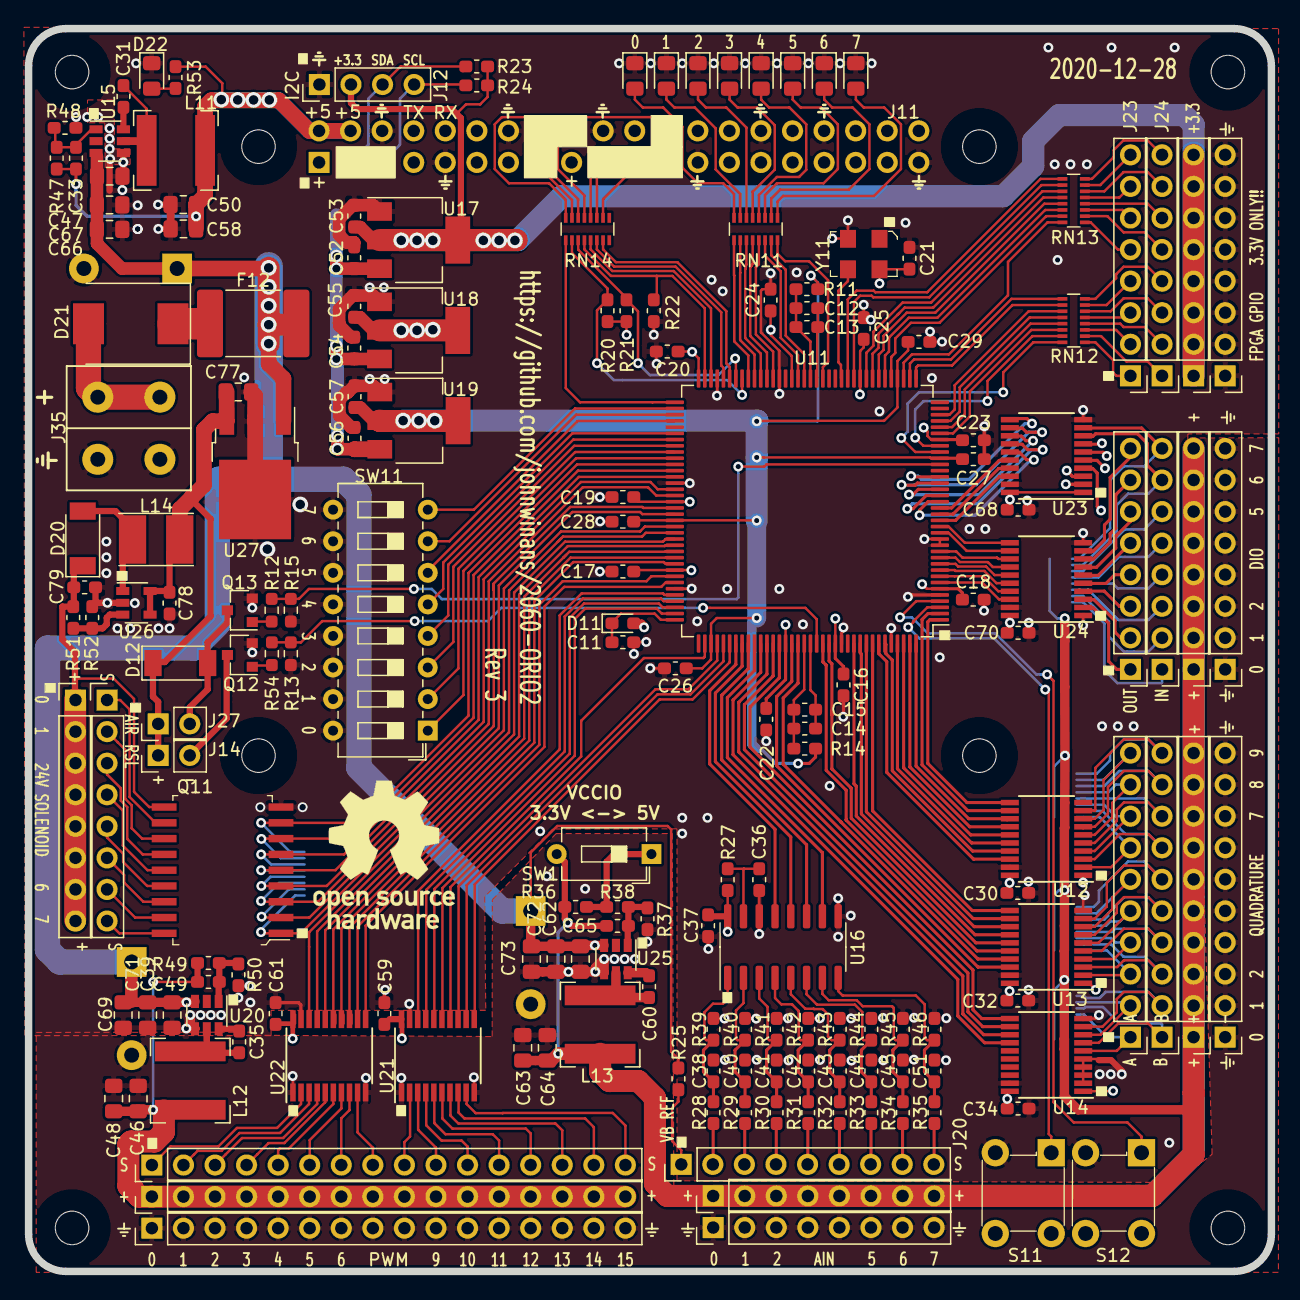
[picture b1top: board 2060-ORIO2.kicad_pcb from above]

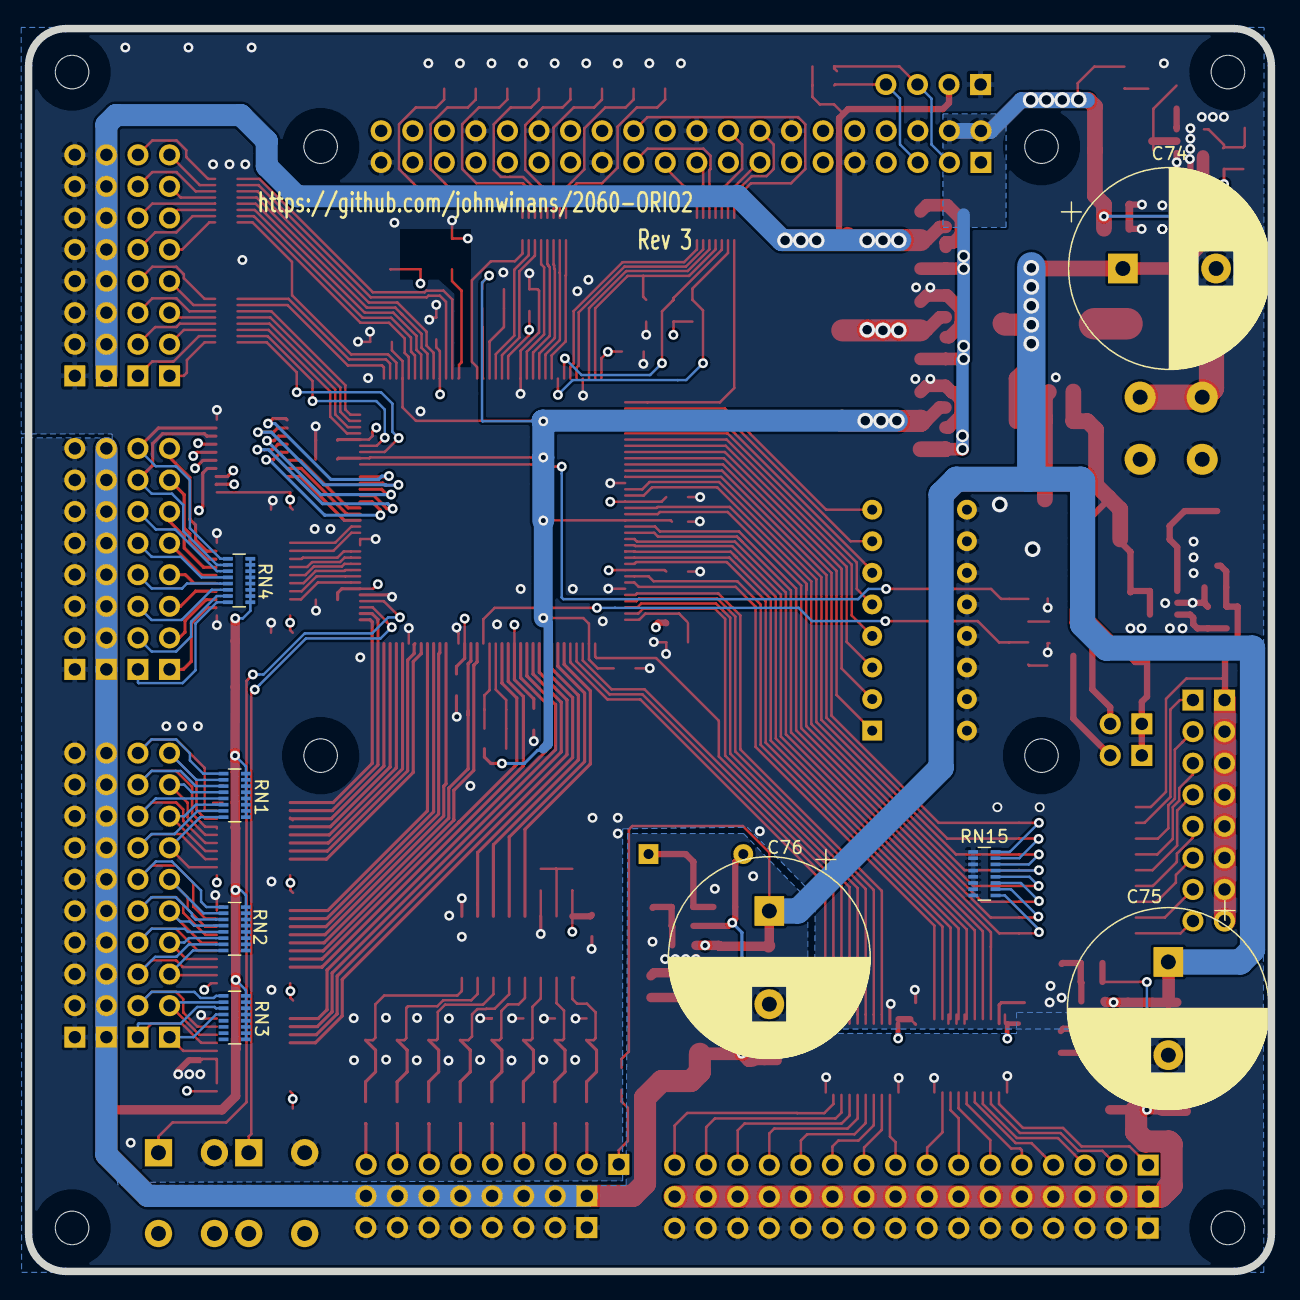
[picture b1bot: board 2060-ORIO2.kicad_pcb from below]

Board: 4 copper layers, 100.0 x 100.0 mm, 195 parts (8 on the bottom side), 254 nets.

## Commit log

2020-06-05 Checkpoint draft.
2020-06-08 checkpoint
2020-06-08 Add link to PCB image.
2020-06-08 Dev checkpoint (first version passing DRC)
2020-06-09 Part value & BOM cleanup.
2020-06-10 Added a pdf of the schematic.
2020-06-10 Checkpoint before re-annotate.
2020-06-10 Re-annotate schematic, clean silks, add NT1.
2020-06-10 Added power LED & GND plane vias.
2020-06-11 Fuses, 4-layer, RSL, 86 the Solenoid GND,
2020-06-13 Added pul;lup resistors on DIN level shifters.
2020-06-14 Cosmetic silkscreen changes.
2020-06-17 Final BOM review & corrections to values.
2020-06-26 Change ADC ref voltage resistor to 100 ohms.
2020-06-26 Add the updated cache.
2020-07-18 Change regulators & add current limiters.
2020-07-20 Change +BATT voltage divider to /6.
2020-07-20 Adjust solenoid connector position.
2020-07-20 Version 2.1 As ordered from JLCPCB.
2020-07-29 Replace AOZ2151TQI-19 regulators with AP63300WU-7
2020-07-29 Remove Rev 1 gerbers.
2020-07-30 Revision 2 as ordered from JLCPCB
2020-12-29 Move the PI connector, add filter caps, & tweak current limiter.
2020-12-29 Change 12V LDO, header & cap clearance
2021-01-17 Add project description.

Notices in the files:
2060-ORIO2.sch:
If you chose to manufacture products based on this design, please notify me (see license section 4.2) via john@winans.org
